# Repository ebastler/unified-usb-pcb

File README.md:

# Unified USB type-C PCB

## Changelog
* 22.11.2020: Simple PCB works, battery PCB is broken. Schematic has been fixed, PCB not. Fix will follow once I find time.
* 09.11.2022: Battery PCB should be fixed, but is untested - I applied the same modifications I previously bodge-wired to earlier protos. The simple PCB now also outputs 5V on the VBUS sense pin, allowing the ZMK Isometria to work with it. I also re-created production files since jlcpcb capabilities increased and they can now assemble everything on these boards. The project is mostly considered abandoned, as I moved to including all battery related circuitry on the main keyboard PCB by now. Still wanted to fix this old project of mine.

A collection of compatible USB-C (2.0) daughterboards with different capabilities, intended to be used in custom mechanical keyboards. All feature the same mechanical dimensions and mounting holes, as well as the same connector leading to the main keyboard PCB and can therefore be exchanged depending on the requeirements.

|||
|:----------------------------------------:|:----------------------------------------:|
|Simple PCB |Battery PCB|

### [Plain USB PCB](unified-usb-pcb_simple)
The simplest and cheapest of the three is just a plain USB breakout board, connecting a USB type C receptacle to a JST SH header for the main keyboard.
 * USB type C
 * SRV-05 TVS on the USB data lines for ESD protection
 * 5 pin JST SH header connecting to the main keyboard PCB

### [Li-Ion PCB](unified-usb-pcb_batt)
This PCB is intended for true wireless use of the keyboard, giving hours of autonomous operation (if a sufficiently large battery is chosen). The battery can be recharged either using the USB-C connector (which can also be used for data) or a QI receiver built into the keyboards base.
 * USB type C
 * JST SH 2-pin input for QI Receiver
 * SRV-05 TVS on the USB data lines for ESD protection
 * JST SH 2-pin header to connect a single Li-Ion or Li-Poly cell
 * TP4056 as a battery charger, DW01 for protection
 * A JST SH 2-pin header allows fo the use of a thermistor to measure cell temperature
 * A sense-wire allows the main controller to check if the battery is currently being charged
 * Solder jumpers to bridge the USB Schottky if no QI receiver is used, as well as the thermistor if the user chooses to use the battery without thermal protection
 * 5 pin JST SH header connecting to the main keyboard PCB

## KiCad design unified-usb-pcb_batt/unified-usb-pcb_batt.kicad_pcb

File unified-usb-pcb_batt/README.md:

# Li-Ion PCB

This PCB is intended for true wireless use of the keyboard, giving hours of autonomous operation (if a sufficiently large battery is chosen). The battery can be recharged either using the USB-C connector (which can also be used for data) or a QI receiver built into the keyboards base.

## Features
 * USB type C
 * JST SH 2-pin input for QI Receiver
 * SRV-05 TVS on the USB data lines for ESD protection
 * JST SH 2-pin header to connect a single Li-Ion or Li-Poly cell
 * TP4056 as a battery charger, DW01 for protection
 * A JST SH 2-pin header allows fo the use of a thermistor to measure cell temperature
 * A sense-wire allows the main controller to check if the battery is currently being charged
 * Solder jumpers to bridge the USB Schottky if no QI receiver is used, as well as the thermistor if the user chooses to use the battery without thermal protection
 * 5 pin JST SH header connecting to the main keyboard PCB

 ## Relevant parts for assembly/customisation

 * Connector J1: QI input, JST SH (SMD, horizontal, 2 Pins. Pin1: GND, Pin2: 5V)
 * Connector J2: USB-C connector (HRO TYPE-C-31-M-12)
 * Connector J3: USB output to main PCB, JST SH (SMD, horizontal, 5 Pins. Pin1: GND, Pin2: D+, Pin3: D-, Pin4: battery voltage, Pin5: charge-sense pin)
 * Connector J4: Battery connector, JST SH (SMD, horizontal, 2 Pins. Pin1: GND, Pin2: Positive)
 * Connector J5: Battery thermistor, JST SH (SMD, horizontal, 2 Pins. Pin1: signal, Pin2: GND (not needed for 3 wire batteries))
 * Jumper JP1: Bridge if no QI is intended to avoid losses over the USB Schottky
 * Jumper JP2: Bridge if you are using an unsupported or no thermistor (the PCB is designed for 10k with a beta of ~ 3500-4000)
 * Switch SW1: Power-switch to cut the battery. [ECE ESP3020](https://www.ece.com.tw/en/switches/slide-switch/56). May be hard to source, but I could not find any similar part that suited this application. Short the 2 pins closer to the JSTs together if you are not using a switch (-> always on).

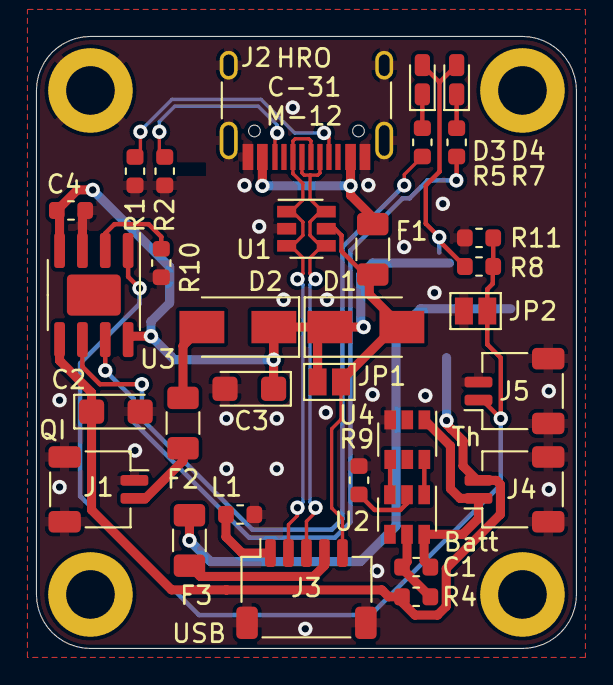
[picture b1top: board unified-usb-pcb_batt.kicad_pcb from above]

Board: 2 copper layers, 30.0 x 34.0 mm, 37 parts (1 on the bottom side), 25 nets.

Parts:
C1, C4: 100n; C_0603_1608Metric
C2, C3: 10u; CP_EIA-3216-18_Kemet-A
D1, D2: SS34; D_SMA
D3: green; LED_0603_1608Metric_Castellated
D4: orange; LED_0603_1608Metric_Castellated
F1, F2, F3: SCF075-1206R; Fuse_1206_3216Metric
H1, H2, H3, H4: MountingHole_Pad; MountingHole_2.7mm_M2.5_DIN965_Pad
J1: QI; JST_SH_SM02B-SRSS-TB_1x02-1MP_P1.00mm_Horizontal
J2: USB_C_Receptacle_USB2.0; USB_C_Receptacle_HRO_TYPE-C-31-M-12
J3: USB_Out; JST_SH_SM05B-SRSS-TB_1x05-1MP_P1.00mm_Horizontal
J4: BATT; JST_SH_SM02B-SRSS-TB_1x02-1MP_P1.00mm_Horizontal
J5: THERM; JST_SH_SM02B-SRSS-TB_1x02-1MP_P1.00mm_Horizontal
JP1: No QI; SolderJumper-2_P1.3mm_Open_Pad1.0x1.5mm
JP2: No thermistor; SolderJumper-2_P1.3mm_Open_Pad1.0x1.5mm
L1: PBY160808T-181Y-N; L_0603_1608Metric
R1, R2: 5,1k; R_0603_1608Metric
R4: 100; R_0603_1608Metric
R5, R7: 2,7k; R_0603_1608Metric
R8: 3.3k; R_0603_1608Metric
R9: 1k; R_0603_1608Metric
R10: 1,8k; R_0603_1608Metric
R11: 22k; R_0603_1608Metric
SW1: SW_SPDT; ESP3020
U1: SRV05-4; SOT-23-6
U2: DW01A; SOT-23-6
U3: TP4056; SOIC-8-1EP_3.9x4.9mm_P1.27mm_EP2.29x3mm
U4: FS8205; SOT-23-6

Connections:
+5V: C3.1, C4.1, D1.1 (K), D2.1 (K), D3.2 (A), D4.2 (A), JP1.1 (A), R8.2, SW1.1 (A), U3.4 (VCC), U3.8 (CE)
GND: J3.1, L1.1
GNDPWR: C2.2, C3.2, C4.2, H4.1, J1.1, J1.MP (MountPin), J2.A1 (GND), J2.A12 (GND), J2.B1 (GND), J2.B12 (GND), J2.S1 (SHIELD), J3.MP (MountPin), J4.MP (MountPin), J5.2, J5.MP (MountPin), JP2.2 (B), L1.2, R1.1, R2.1, R9.1, R10.1, R11.1, U1.2 (VN), U3.3 (GND), U4.3 (S2)
unnamed: C2.1, J4.2, R4.2, SW1.3 (C), U3.5 (BAT)
unnamed: D2.2 (A), F2.1
unnamed: D3.1 (K), R5.2
unnamed: D4.1 (K), R7.2
unnamed: F2.2, J1.2
unnamed: F3.1, J3.4
unnamed: F1.2, J2.A4 (VBUS), J2.A9 (VBUS), J2.B4 (VBUS), J2.B9 (VBUS)
unnamed: J2.A5 (CC1), R1.2
unnamed: J2.B5 (CC2), R2.2
unnamed: J5.1, JP2.1 (A), R8.1, R11.2, U3.1 (TEMP)
unnamed: R5.1, U3.6 (STDBY)
unnamed: R7.1, U3.7 (CHRG)
unnamed: R10.2, U3.2 (PROG)
unnamed: U2.1 (OD), U4.6 (G1)
unnamed: R9.2, U2.2 (CSI)
unnamed: U2.3 (OC), U4.4 (G2)
unnamed: C1.1, R4.1, U2.5 (VDD)
unnamed: C1.2, J4.1, U2.6 (VSS), U4.1 (S1)
USB_D+: J2.A6 (D+), J2.B6 (D+), J3.2, U1.1 (IO1), U1.3 (IO2)
USB_D-: J2.A7 (D-), J2.B7 (D-), J3.3, U1.4 (IO3), U1.6 (IO4)
VBUS: D1.2 (A), F1.1, J3.5, JP1.2 (B), U1.5 (VP)
VOUT: F3.2, SW1.2 (B)

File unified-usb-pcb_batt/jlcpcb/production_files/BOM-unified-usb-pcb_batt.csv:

Comment,Designator,Footprint,LCSC
SW_SPDT,SW1,ESP3020,/
PBY160808T-181Y-N,L1,L_0603_1608Metric,C114288
"2,7k","R5,R7",R_0603_1608Metric,C13167
DW01A,U2,SOT-23-6,C14213
QI,"J1,J4,J5",JST_SH_SM02B-SRSS-TB_1x02-1MP_P1.00mm_Horizontal,C145954
USB_Out,J3,JST_SH_SM05B-SRSS-TB_1x05-1MP_P1.00mm_Horizontal,C145957
100n,"C1,C4",C_0603_1608Metric,C14663
TP4056,U3,SOIC-8-1EP_3.9x4.9mm_P1.27mm_EP2.29x3mm,C16581
USB_C_Receptacle_USB2.0,J2,USB_C_Receptacle_HRO_TYPE-C-31-M-12,C165948
SCF075-1206R,"F1,F2,F3",Fuse_1206_3216Metric,C20987
1k,R9,R_0603_1608Metric,C21190
100,R4,R_0603_1608Metric,C22775
orange,D4,LED_0603_1608Metric_Castellated,C2286
3.3k,R8,R_0603_1608Metric,C22978
"5,1k","R1,R2",R_0603_1608Metric,C23186
22k,R11,R_0603_1608Metric,C31850
FS8205,U4,SOT-23-6,C32254
"1,8k",R10,R_0603_1608Metric,C4177
10u,"C2,C3",CP_EIA-3216-18_Kemet-A,C7171
green,D3,LED_0603_1608Metric_Castellated,C72043
SRV05-4,U1,SOT-23-6,C85364
SS34,"D1,D2",D_SMA,C8678

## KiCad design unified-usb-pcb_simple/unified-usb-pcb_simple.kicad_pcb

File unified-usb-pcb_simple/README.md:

# Plain USB PCB

The simplest and cheapest of the three is just a plain USB breakout board, connecting a USB type C receptacle to a JST SH header for the main keyboard.

## Features
 * USB type C
 * SRV-05 TVS on the USB data lines for ESD protection
 * 5 pin JST SH header connecting to the main keyboard PCB

 ## Relevant parts for assembly/customisation

 * Connector J1: USB-C connector (HRO TYPE-C-31-M-12)
 * Connector J2: USB output to main PCB, JST SH (SMD, horizontal, 5 Pins. Pin1: GND, Pin2: D+, Pin3: D-, Pin4: +5V, Pin5: VBUS detection)

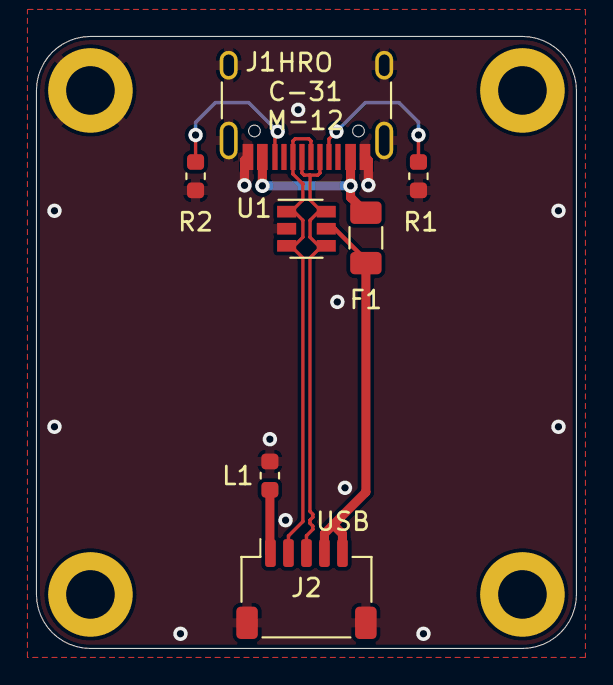
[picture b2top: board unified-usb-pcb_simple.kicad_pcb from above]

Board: 2 copper layers, 30.0 x 34.0 mm, 11 parts (0 on the bottom side), 8 nets.

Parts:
F1: SCF075-1206R; Fuse_1206_3216Metric
H1, H2, H3, H4: MountingHole_Pad; MountingHole_2.7mm_M2.5_DIN965_Pad
J1: USB_C_Receptacle_USB2.0; USB_C_Receptacle_HRO_TYPE-C-31-M-12
J2: USB_Out; JST_SH_SM05B-SRSS-TB_1x05-1MP_P1.00mm_Horizontal
L1: PBY160808T-181Y-N; L_0603_1608Metric
R1, R2: 5.1k; R_0603_1608Metric
U1: SRV05-4; SOT-23-6

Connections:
Earth: H1.1, J1.A1 (GND), J1.A12 (GND), J1.B1 (GND), J1.B12 (GND), J1.S1 (SHIELD), J2.MP (MountPin), L1.2, R1.1, R2.1, U1.2 (VN)
GND: J2.1, L1.1
unnamed: F1.2, J1.A4 (VBUS), J1.A9 (VBUS), J1.B4 (VBUS), J1.B9 (VBUS)
unnamed: J1.A5 (CC1), R1.2
unnamed: J1.B5 (CC2), R2.2
USB_D+: J1.A6 (D+), J1.B6 (D+), J2.2, U1.1 (IO1), U1.3 (IO2)
USB_D-: J1.A7 (D-), J1.B7 (D-), J2.3, U1.4 (IO3), U1.6 (IO4)
VOUT: F1.1, J2.4, J2.5, U1.5 (VP)

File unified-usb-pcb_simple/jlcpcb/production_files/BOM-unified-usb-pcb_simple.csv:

Comment,Designator,Footprint,LCSC
PBY160808T-181Y-N,L1,L_0603_1608Metric,C114288
USB_Out,J2,JST_SH_SM05B-SRSS-TB_1x05-1MP_P1.00mm_Horizontal,C145957
USB_C_Receptacle_USB2.0,J1,USB_C_Receptacle_HRO_TYPE-C-31-M-12,C165948
SCF075-1206R,F1,Fuse_1206_3216Metric,C20987
5.1k,"R1,R2",R_0603_1608Metric,C23186
SRV05-4,U1,SOT-23-6,C85364

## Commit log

2020-04-02 added readme content
2020-04-02 partially completed the battery board
2020-04-03 added thermistor values and charge sense wire
2020-04-03 updated TBD to fit project progress
2020-04-03 added a jumper to disconnect battery
2020-04-07 added submodule for parts
2020-04-07 continued with Li-Ion schematic, initialised pcb
2020-04-07 replaced jumper with smd switch
2020-04-07 added 3d models, changed tp4056 footprint
2020-04-07 added 3d model of switch
2020-04-07 added usb-c submodule
2020-04-07 added 3d model for usb-c header
2020-04-07 moved switch 3d model to submodule
2020-04-08 started working on pcb layout
2020-04-08 finished pcb
2020-04-08 updated TBD section
2020-04-08 added silkscreen text
2020-04-08 added fuse 3d model
2020-04-08 added readme for LiIon PCB
2020-04-08 cosmetic changes
2020-04-08 added thermistor recommended value
2020-04-08 created simple usb pcb
2020-04-08 matched usb trace length
2020-04-08 re-annotaded the schematic
2020-04-08 fixed name on silkscreen
2020-04-08 added .bak
2020-04-08 added ferrite bead, improved usb track matching
2020-04-08 added ferrite bead
2020-04-08 removed .bak
2020-04-08 removed old silkscreen files
2020-04-15 moved outline/holes for usb-c connector to protrude 1 mm
2020-04-19 moved connectors
    in order to less obstruct underglow less
2020-04-26 created plane for usb-shielding below the connector
2020-04-26 resized shield plane
2020-04-26 moved traces for better ground pour, added a probably unneccessary amount of vias
2020-04-26 added jlcpcb part numbers
2020-04-27 added manufacturing files
2020-04-27 changed jumper pad, fixed silk
2020-04-28 added renders
2020-04-28 cropped renders
2020-04-28 rename render
2020-07-07 added a license
2020-07-07 changed pcb thickness from 1.6 to 1mm
2020-08-28 updated submodules
2020-11-22 fixed batt schem, added readme warning about broken pcb
2021-02-08 removed chargesense, added VBUS detection to schematic
2022-11-09 slight rev bump - fixed battery pcb, re-exported new prod files for jlcpcb. Probably last commit, project no longer in active development
2022-11-09 updated readme to reflect recent changes
